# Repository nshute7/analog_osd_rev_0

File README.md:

# analog_osd_rev_0
Analog on-screen display (OSD) board designed in KiCad for MAX7456E derivatives.

This layout was influenced heavily by original work found at https://github.com/night-ghost/minimosd-extra/tree/master/board.

The contribution of this project is to re-implement the analog first-person view (FPV) hardware using a recent parts list available through PCB houses such as JLCPCB.

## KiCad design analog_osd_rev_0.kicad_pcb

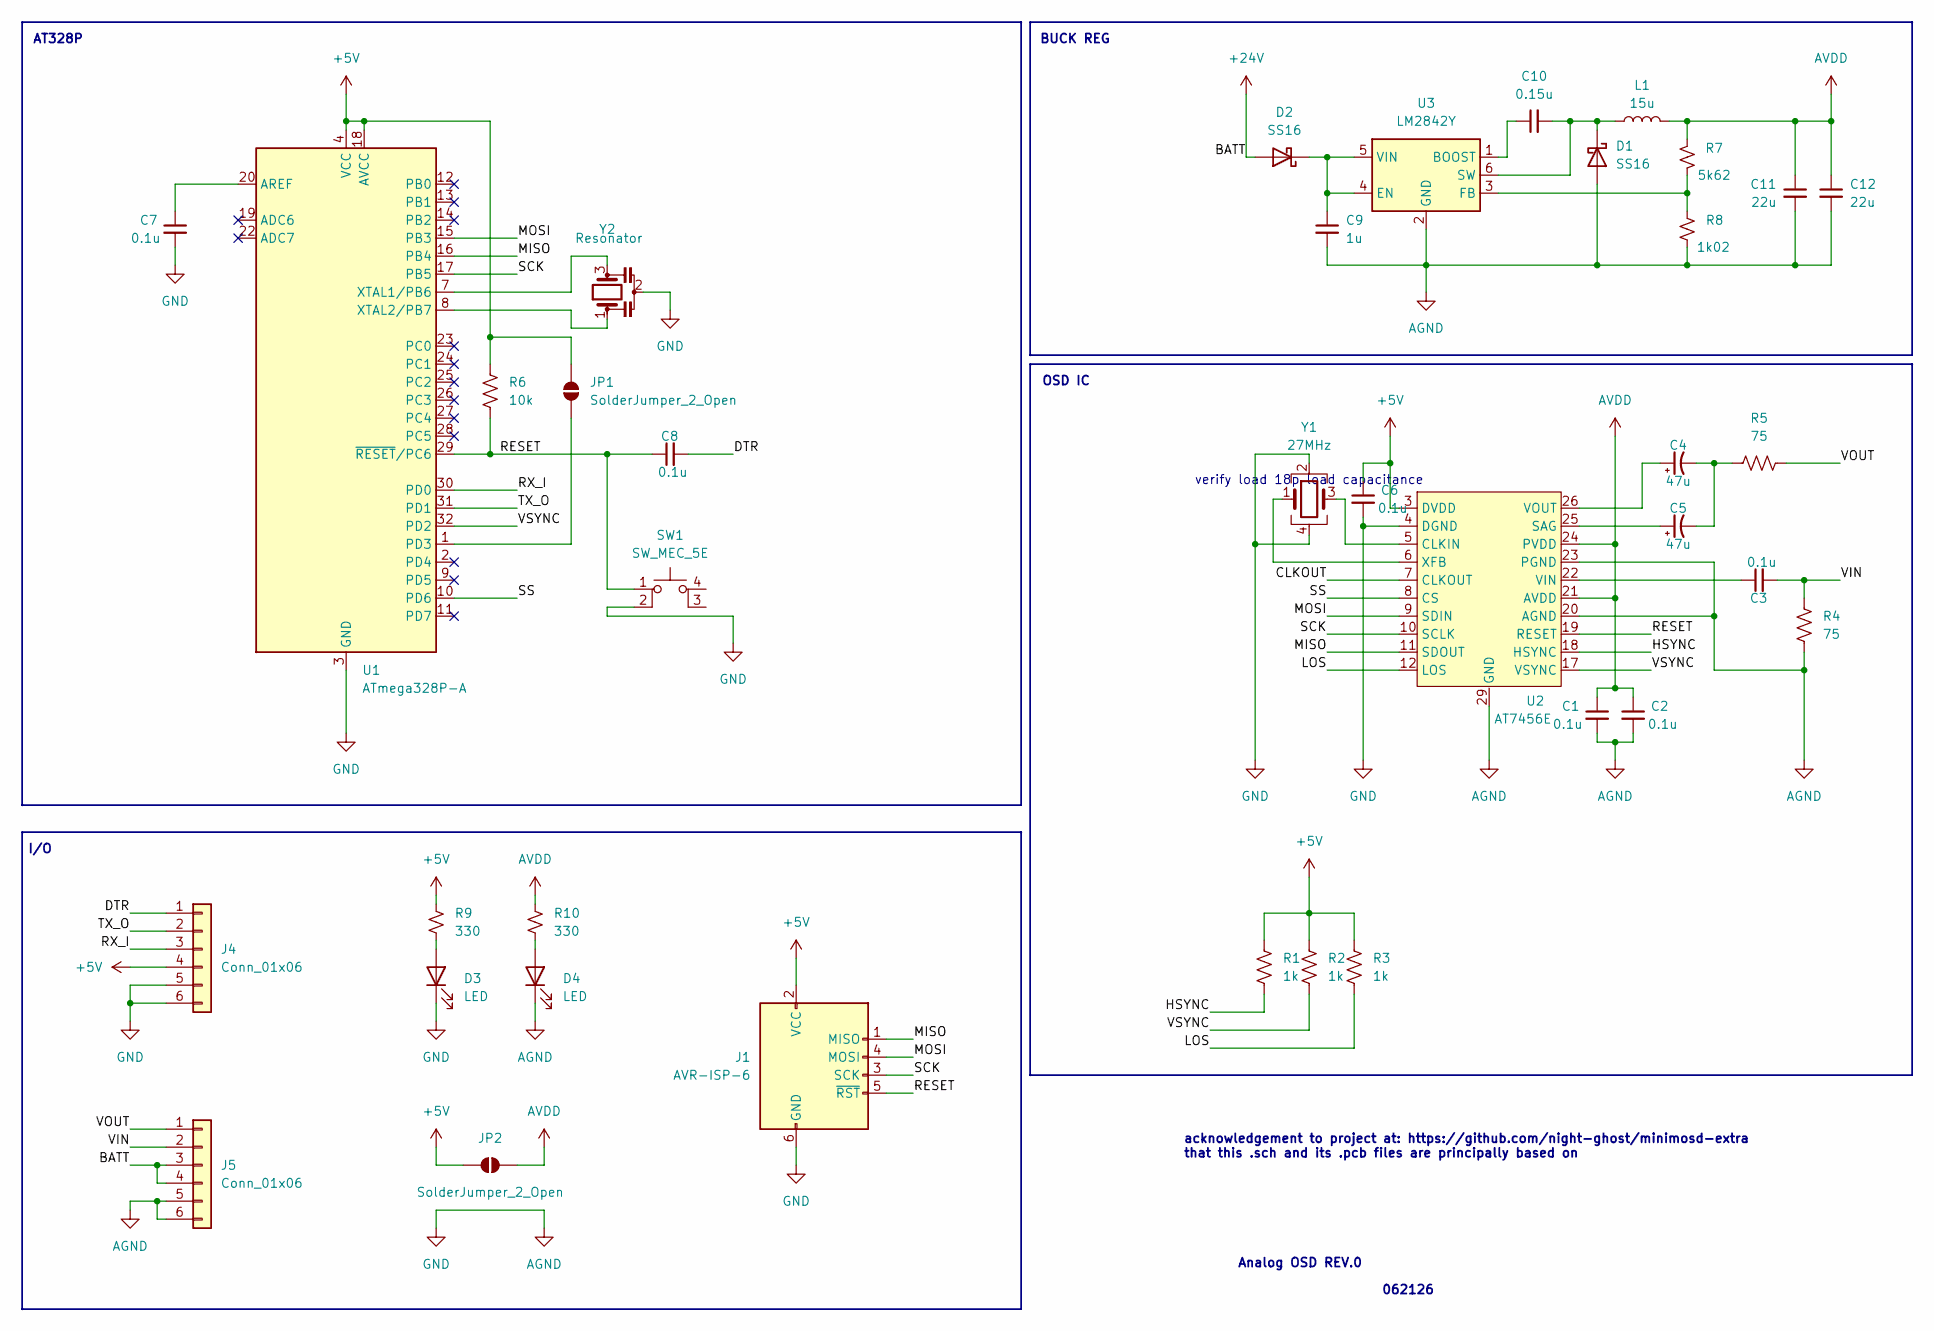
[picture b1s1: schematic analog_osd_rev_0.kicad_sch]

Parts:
C1, C2, C3, C6, C7, C8: 0.1u; C_0402_1005Metric; LCSC PN C307331
C4, C5: 47u; CP_EIA-3216-18_Kemet-A; LCSC PN C7190
C9: 1u; C_0603_1608Metric; LCSC PN C15849
C10: 0.15u; C_0603_1608Metric; LCSC PN C513735
C11, C12: 22u; C_0805_2012Metric; LCSC PN C45783
D1, D2: SS16; D_SMA; LCSC PN C2481
D3: LED; LED_0603_1608Metric; LCSC PN C2287
D4: LED; LED_0603_1608Metric; LCSC PN C2286
J1: AVR-ISP-6; __PinSocket_2x03_P2.54mm_Vertical
J4: Conn_01x06; __PinHeader_1x06_P2.54mm_Vertical
J5: Conn_01x06; __PinSocket_2x03_P2.54mm_Vertical
JP1, JP2: SolderJumper_2_Open; SolderJumper-2_P1.3mm_Open_RoundedPad1.0x1.5mm
L1: 15u; L_Vishay_IFSC-1515AH_4x4x1.8mm; LCSC PN C844950
R1, R2, R3: 1k; R_0603_1608Metric; LCSC PN C21190
R4, R5: 75; R_0603_1608Metric; LCSC PN C4275
R6: 10k; R_0603_1608Metric; LCSC PN C95204
R7: 5k62; R_0603_1608Metric; LCSC PN C23188
R8: 1k02; R_0603_1608Metric; LCSC PN C22831
R9, R10: 330; R_0603_1608Metric; LCSC PN C23138
SW1: SW_MEC_5E; SW_Push_1P1T_NO_Vertical_Wuerth_434133025816; LCSC PN C139797
U1: ATmega328P-A; TQFP-32_7x7mm_P0.8mm; LCSC PN C14877
U2: AT7456E; HTSSOP-28-1EP_4.4x9.7mm_P0.65mm_EP2.75x6.2mm_ThermalVias; LCSC PN C82351
U3: LM2842Y; TSOT-23-6; LCSC PN C30170092
Y1: 27MHz; Crystal_SMD_3225-4Pin_3.2x2.5mm; LCSC PN C2981701
Y2: Resonator; Resonator_SMD_Murata_CSTxExxV-3Pin_3.0x1.1mm; LCSC PN C783275

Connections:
+5V: C6.1, J1.2 (VCC), J4.4, JP1.2 (B), JP2.1 (A), R1.1, R2.1, R3.1, R6.1, R9.1, U1.4 (VCC), U1.6 (VCC), U1.18 (AVCC), U2.3 (DVDD)
+24V: D2.2 (A), J5.3, J5.4
/CLKOUT: U2.7 (CLKOUT)
/DTR: C8.2, J4.1
/HSYNC: R1.2, U2.18 (HSYNC)
/LOS: R3.2, U2.12 (LOS)
/MISO: J1.1 (MISO), U1.16 (PB4), U2.11 (SDOUT)
/MOSI: J1.4 (MOSI), U1.15 (PB3), U2.9 (SDIN)
/RESET: C8.1, J1.5 (~RST), R6.2, SW1.1, U1.29 (~RESET/PC6), U2.19 (RESET)
/RX_I: J4.3, U1.30 (PD0)
/SCK: J1.3 (SCK), U1.17 (PB5), U2.10 (SCLK)
/SS: U1.10 (PD6), U2.8 (CS)
/TX_O: J4.2, U1.31 (PD1)
/VIN: C3.2, J5.2, R4.1
/VOUT: J5.1, R5.2
/VSYNC: R2.2, U1.32 (PD2), U2.17 (VSYNC)
AGND: C1.2, C2.2, C6.2, C7.2, C9.2, C11.2, C12.2, D1.2 (A), D3.1 (K), D4.1 (K), J1.6 (GND), J4.5, J4.6, J5.5, J5.6, R4.2, R8.2, SW1.2, U1.3 (GND), U1.5 (GND), U1.21 (GND), U2.4 (DGND), U2.20 (AGND), U2.23 (PGND), U2.29 (GND), U3.2 (GND), Y1.2, Y1.4, Y2.2
AVDD: C1.1, C2.1, C11.1, C12.1, JP2.2 (B), L1.2, R7.1, R10.1, U2.21 (AVDD), U2.24 (PVDD)
unnamed: C4.2, C5.2, R5.1
unnamed: C10.2, D1.1 (K), L1.1, U3.6 (SW)
unnamed: C9.1, D2.1 (K), U3.4 (EN), U3.5 (VIN)
unnamed: D3.2 (A), R9.2
unnamed: D4.2 (A), R10.2
unnamed: JP1.1 (A), U1.1 (PD3)
unnamed: C7.1, U1.20 (AREF)
unnamed: U1.7 (XTAL1/PB6), Y2.3
unnamed: U1.8 (XTAL2/PB7), Y2.1
unnamed: U2.5 (CLKIN), Y1.3
unnamed: C5.1, U2.25 (SAG)
unnamed: C3.1, U2.22 (VIN)
unnamed: C4.1, U2.26 (VOUT)
unnamed: U2.6 (XFB), Y1.1
unnamed: C10.1, U3.1 (BOOST)
unnamed: R7.2, R8.1, U3.3 (FB)

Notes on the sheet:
OSD IC
Analog OSD REV.0
BUCK REG
AT328P
verify load 18p load capacitance
I/O
062126
acknowledgement to project at: https://github.com/night-ghost/minimosd-extra that this .sch and its .pcb files are principally based on

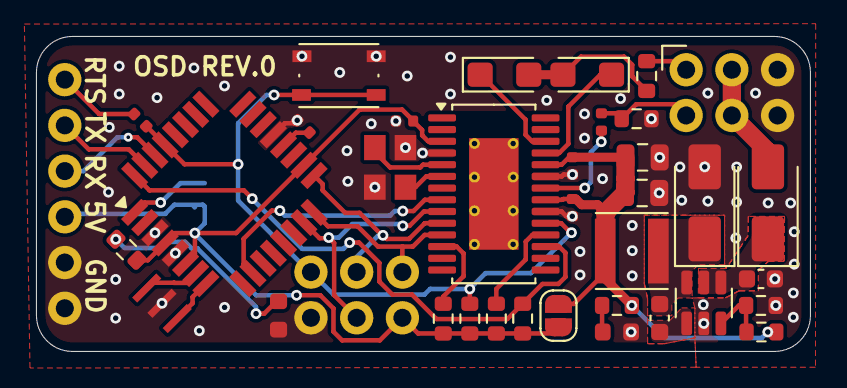
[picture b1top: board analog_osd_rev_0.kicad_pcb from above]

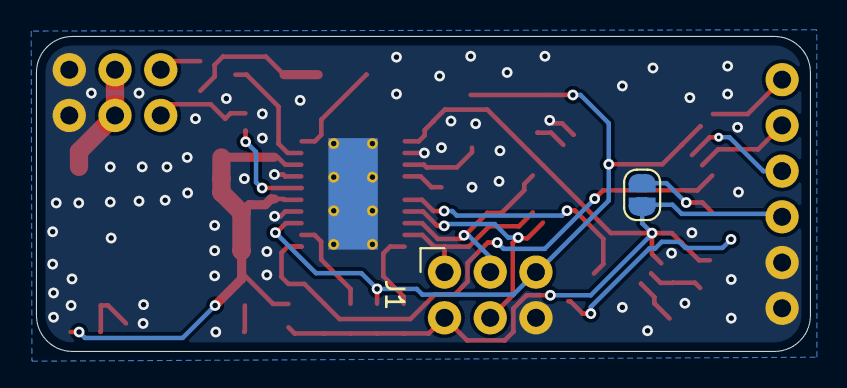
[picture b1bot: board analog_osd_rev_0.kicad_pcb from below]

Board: 2 copper layers, 43.0 x 17.5 mm, 38 parts (2 on the bottom side), 33 nets.
